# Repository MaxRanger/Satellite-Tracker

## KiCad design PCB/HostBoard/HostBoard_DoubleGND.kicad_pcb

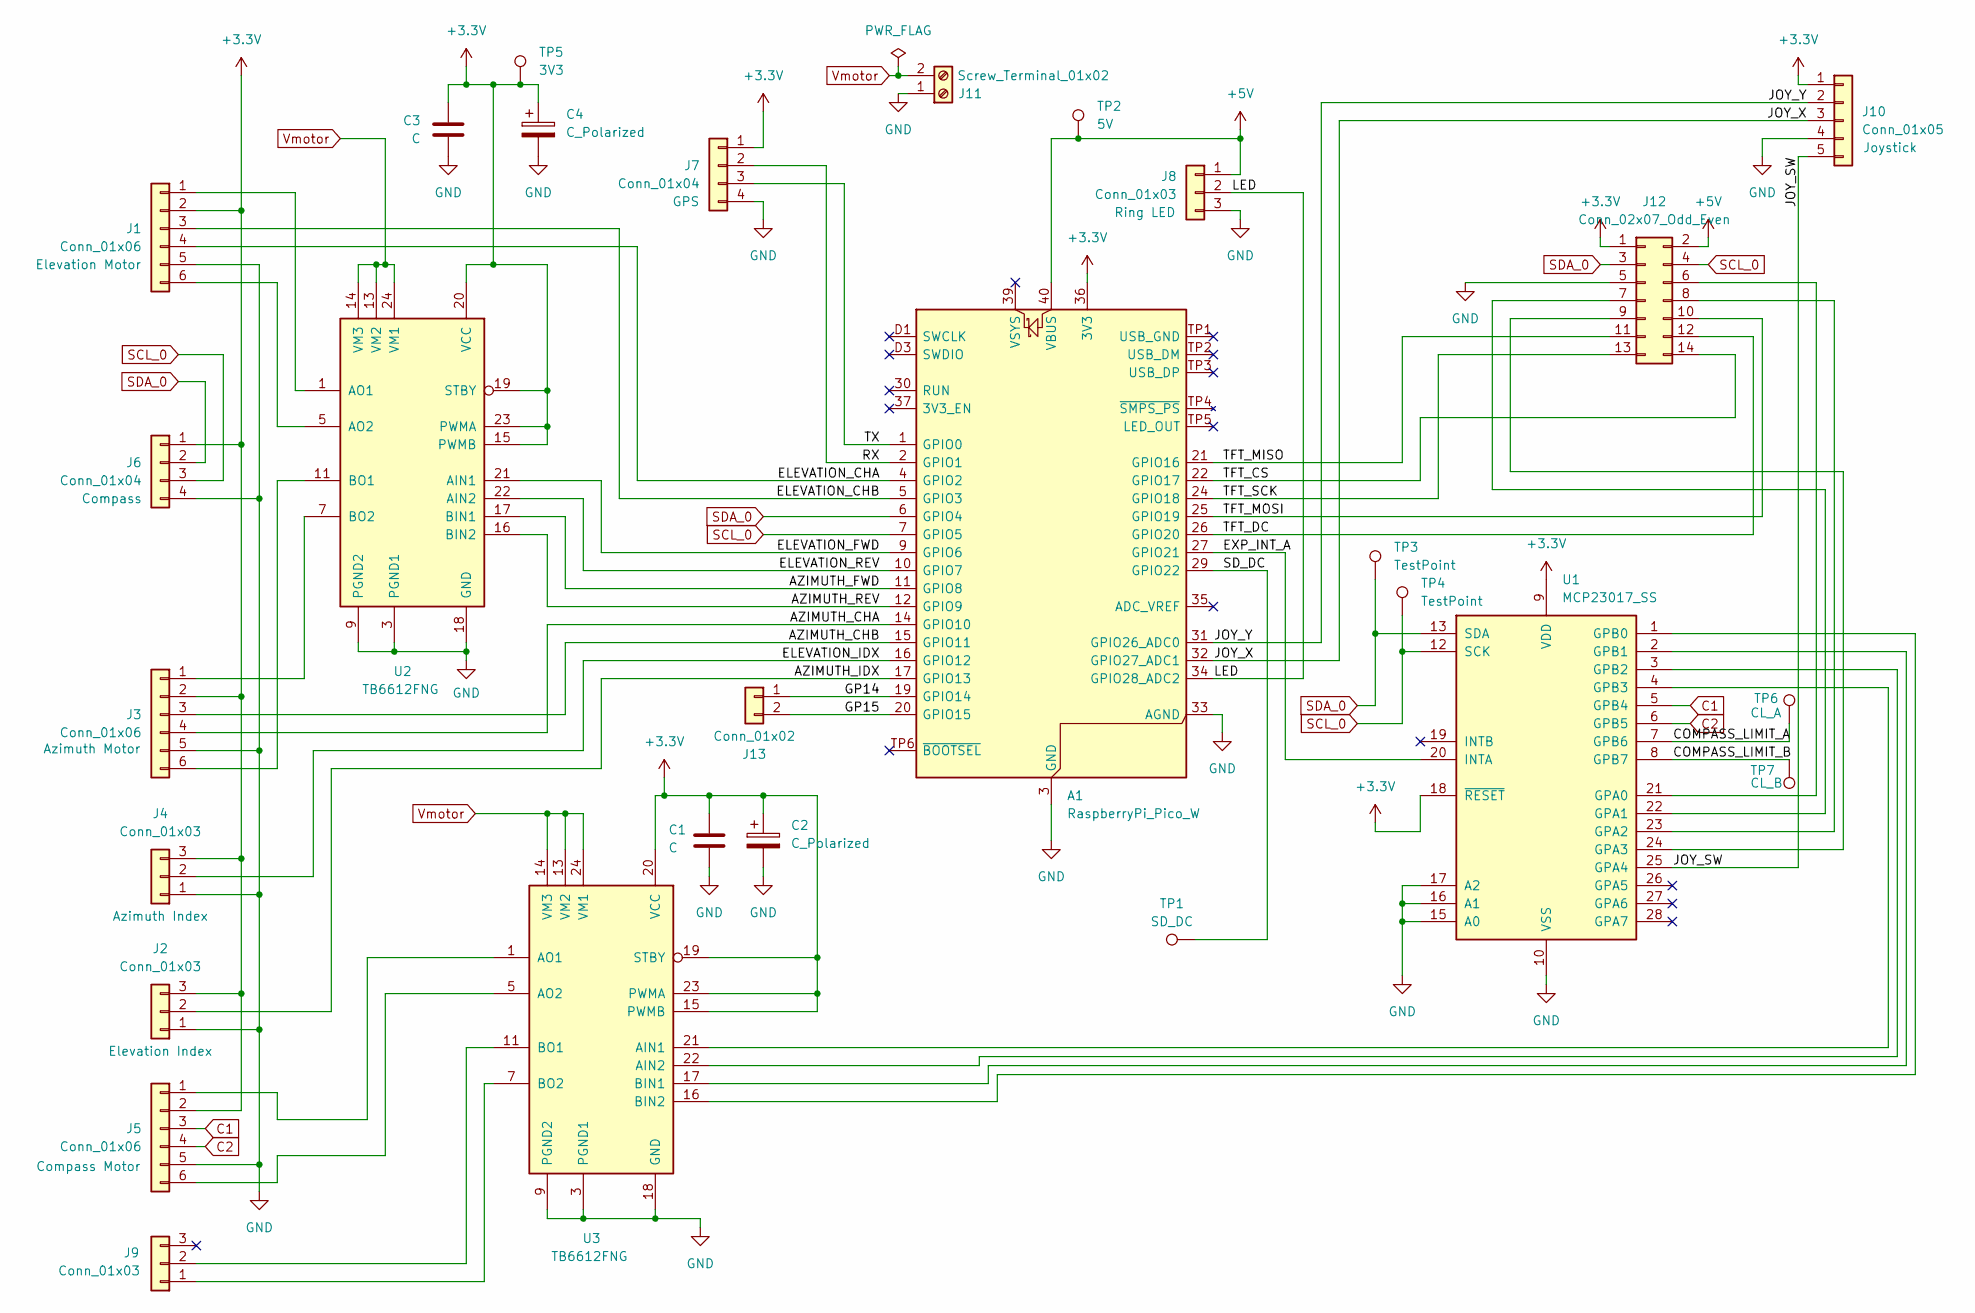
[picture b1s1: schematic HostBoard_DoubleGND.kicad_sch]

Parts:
A1: RaspberryPi_Pico_W; RaspberryPi_Pico_Common_THT
C1, C3: C; C_0805_2012Metric_Pad1.18x1.45mm_HandSolder
C2, C4: C_Polarized; C_0805_2012Metric_Pad1.18x1.45mm_HandSolder
J1, J3, J5: Conn_01x06; JST_EH_S6B-EH_1x06_P2.50mm_Horizontal
J2, J4, J8: Conn_01x03; JST_EH_S3B-EH_1x03_P2.50mm_Horizontal
J6, J7: Conn_01x04; JST_EH_S4B-EH_1x04_P2.50mm_Horizontal
J9: Conn_01x03; PinHeader_1x03_P2.54mm_Vertical
J10: Conn_01x05; JST_EH_S5B-EH_1x05_P2.50mm_Horizontal
J11: Screw_Terminal_01x02; TerminalBlock_Xinya_XY308-2.54-2P_1x02_P2.54mm_Horizontal
J12: Conn_02x07_Odd_Even; PinHeader_2x07_P2.54mm_Vertical
J13: Conn_01x02; PinHeader_1x02_P2.54mm_Vertical
TP1: SD_DC; PinHeader_1x01_P2.54mm_Vertical
TP2: 5V; PinHeader_1x01_P2.54mm_Vertical
TP3, TP4: TestPoint; TestPoint_Pad_1.0x1.0mm
TP5: 3V3; PinHeader_1x01_P2.54mm_Vertical
TP6: CL_A; TestPoint_Pad_1.0x1.0mm
TP7: CL_B; TestPoint_Pad_1.0x1.0mm
U1: MCP23017_SS; SSOP-28_5.3x10.2mm_P0.65mm
U2, U3: TB6612FNG; SSOP-24_5.3x8.2mm_P0.65mm

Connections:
+3.3V: A1.36 (3V3), C1.1, C2.1, C3.1, C4.1, J1.2, J2.3, J3.2, J4.3, J5.2, J6.1, J7.1, J10.1, J12.1, TP5.1, U1.9 (VDD), U1.18 (~RESET), U2.15 (PWMB), U2.19 (STBY), U2.20 (VCC), U2.23 (PWMA), U3.15 (PWMB), U3.19 (STBY), U3.20 (VCC), U3.23 (PWMA)
+5V: A1.40 (VBUS), J8.1, J12.2, TP2.1
/AZIMUTH_CHA: A1.14 (GPIO10), J3.4
/AZIMUTH_CHB: A1.15 (GPIO11), J3.3
/AZIMUTH_FWD: A1.11 (GPIO8), U2.17 (BIN1)
/AZIMUTH_IDX: A1.17 (GPIO13), J2.2
/AZIMUTH_REV: A1.12 (GPIO9), U2.16 (BIN2)
/COMPASS_LIMIT_A: TP6.1, U1.7 (GPB6)
/COMPASS_LIMIT_B: TP7.1, U1.8 (GPB7)
/ELEVATION_CHA: A1.4 (GPIO2), J1.4
/ELEVATION_CHB: A1.5 (GPIO3), J1.3
/ELEVATION_FWD: A1.9 (GPIO6), U2.21 (AIN1)
/ELEVATION_IDX: A1.16 (GPIO12), J4.2
/ELEVATION_REV: A1.10 (GPIO7), U2.22 (AIN2)
/EXP_INT_A: A1.27 (GPIO21), U1.20 (INTA)
/GP14: A1.19 (GPIO14), J13.1
/GP15: A1.20 (GPIO15), J13.2
/JOY_SW: J10.5, U1.25 (GPA4)
/JOY_X: A1.32 (GPIO27_ADC1), J10.3
/JOY_Y: A1.31 (GPIO26_ADC0), J10.2
/LED: A1.34 (GPIO28_ADC2), J8.2
/RX: A1.2 (GPIO1), J7.2
/SD_DC: A1.29 (GPIO22), TP1.1
/TFT_CS: A1.22 (GPIO17), J12.14
/TFT_DC: A1.26 (GPIO20), J12.12
/TFT_MISO: A1.21 (GPIO16), J12.11
/TFT_MOSI: A1.25 (GPIO19), J12.10
/TFT_SCK: A1.24 (GPIO18), J12.13
/TX: A1.1 (GPIO0), J7.3
C1: J5.3, U1.5 (GPB4)
C2: J5.4, U1.6 (GPB5)
GND: A1.3 (GND), A1.8 (GND), A1.13 (GND), A1.18 (GND), A1.23 (GND), A1.28 (GND), A1.33 (AGND), A1.38 (GND), A1.D2 (GND), C1.2, C2.2, C3.2, C4.2, J1.5, J2.1, J3.5, J4.1, J5.5, J6.4, J7.4, J8.3, J10.4, J11.1, J12.5, U1.10 (VSS), U1.15 (A0), U1.16 (A1), U1.17 (A2), U2.3 (PGND1), U2.4 (PGND1), U2.9 (PGND2), U2.10 (PGND2), U2.18 (GND), U3.3 (PGND1), U3.4 (PGND1), U3.9 (PGND2), U3.10 (PGND2), U3.18 (GND)
unnamed: J1.1, U2.1 (AO1), U2.2 (AO1)
unnamed: J1.6, U2.5 (AO2), U2.6 (AO2)
unnamed: J3.1, U2.7 (BO2), U2.8 (BO2)
unnamed: J3.6, U2.11 (BO1), U2.12 (BO1)
unnamed: J5.1, U3.1 (AO1), U3.2 (AO1)
unnamed: J5.6, U3.5 (AO2), U3.6 (AO2)
unnamed: J9.1, U3.7 (BO2), U3.8 (BO2)
unnamed: J9.2, U3.11 (BO1), U3.12 (BO1)
unnamed: J12.6, U1.21 (GPA0)
unnamed: J12.7, U1.22 (GPA1)
unnamed: J12.8, U1.23 (GPA2)
unnamed: J12.9, U1.24 (GPA3)
unnamed: U1.1 (GPB0), U3.16 (BIN2)
unnamed: U1.2 (GPB1), U3.17 (BIN1)
unnamed: U1.3 (GPB2), U3.22 (AIN2)
unnamed: U1.4 (GPB3), U3.21 (AIN1)
SCL_0: A1.7 (GPIO5), J6.3, J12.4, TP4.1, U1.12 (SCK)
SDA_0: A1.6 (GPIO4), J6.2, J12.3, TP3.1, U1.13 (SDA)
Vmotor: J11.2, U2.13 (VM2), U2.14 (VM3), U2.24 (VM1), U3.13 (VM2), U3.14 (VM3), U3.24 (VM1)

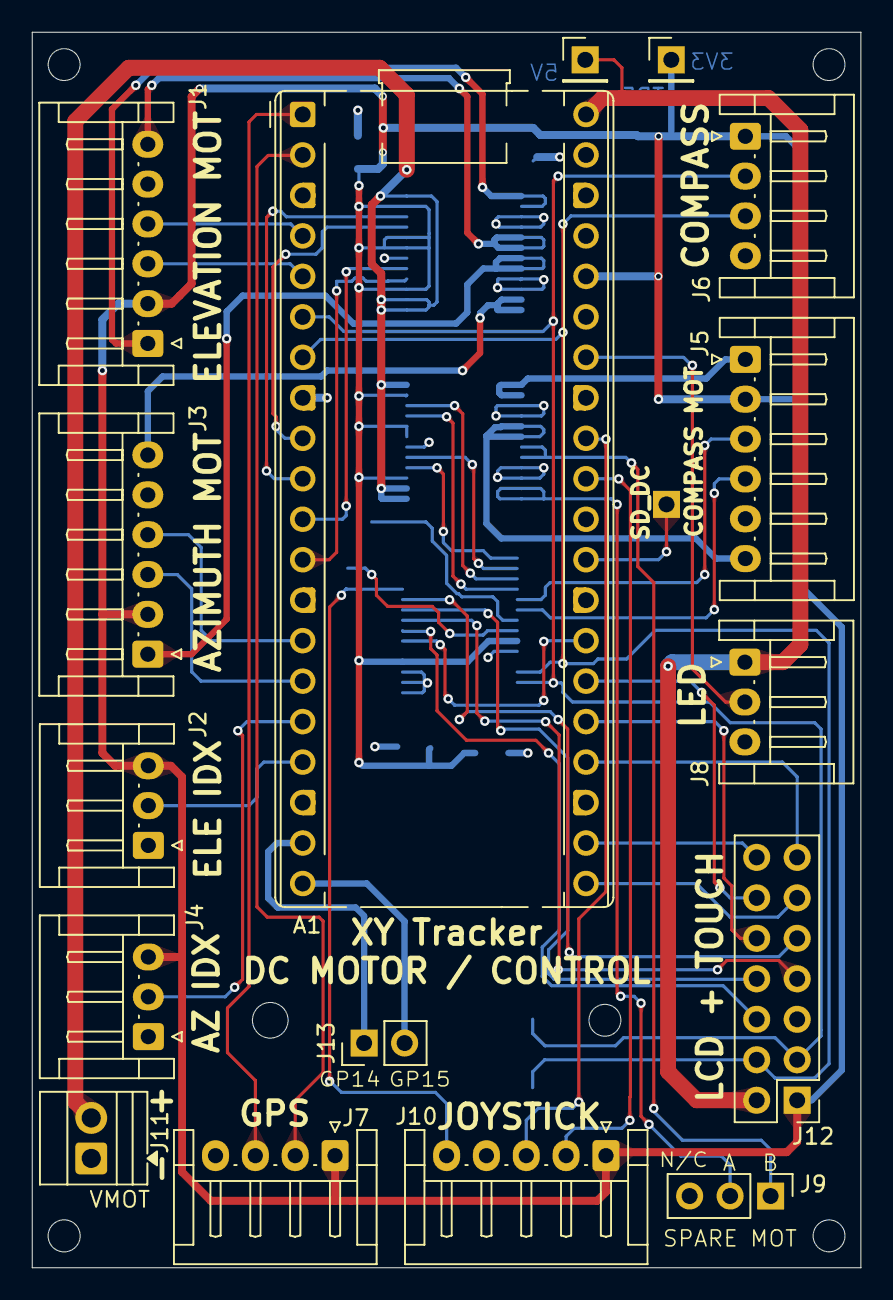
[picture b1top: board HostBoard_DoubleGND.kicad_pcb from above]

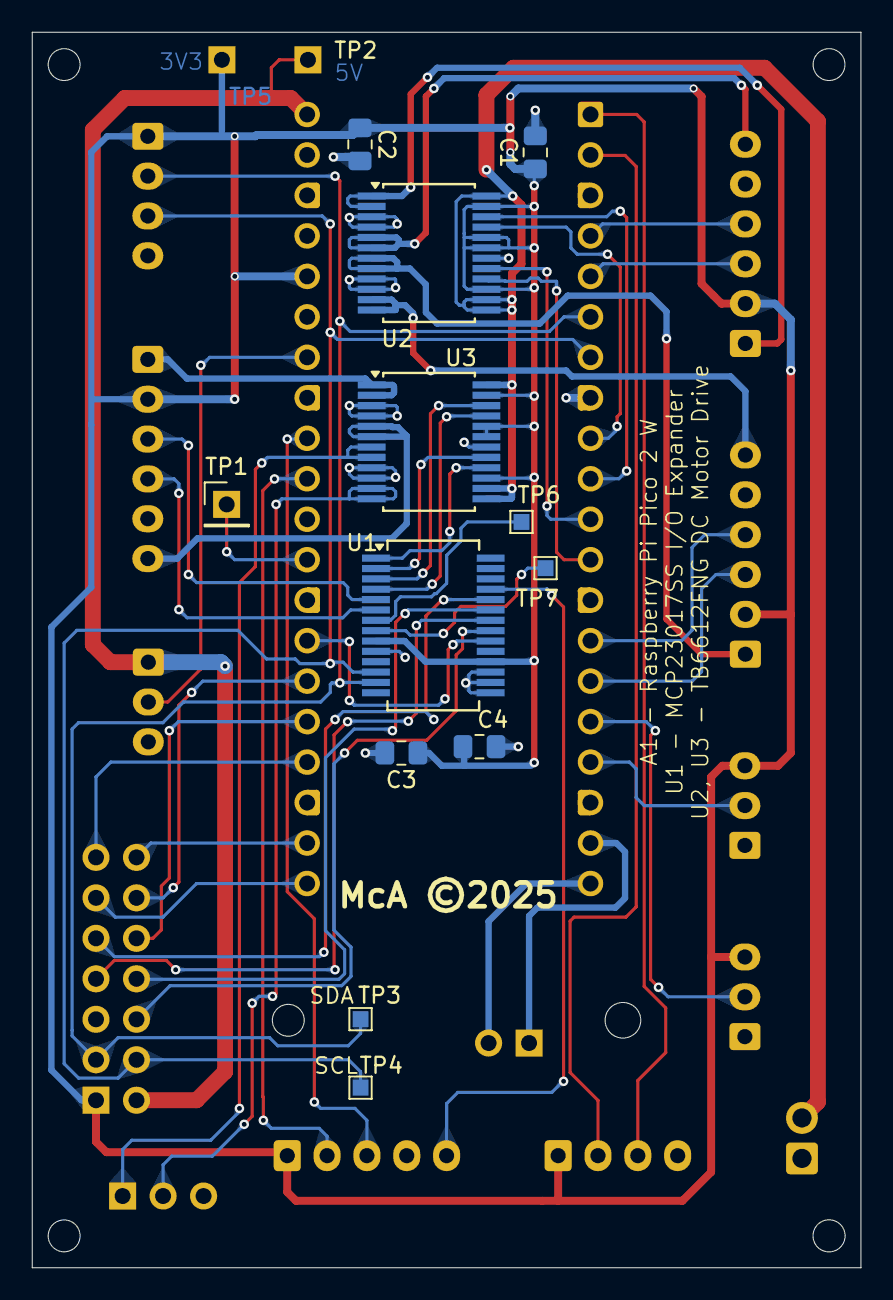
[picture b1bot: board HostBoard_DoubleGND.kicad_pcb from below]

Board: 4 copper layers, 52.0 x 77.5 mm, 28 parts (12 on the bottom side), 51 nets.

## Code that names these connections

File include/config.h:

/*
 * config.h - Configuration and Pin Definitions
 */

#ifndef CONFIG_H
#define CONFIG_H


// ============================================================================
// Cables and Connectors for prototype model 1
// ============================================================================
// Joystick - 5 pin. BLACK=GND, WHITE=VCC, GREY=X[GP26 (ADC0) Pin 32], PURPLE=Y[GP27 (ADC1) Pin 31], BLUE=Button
// GPS: 5 pin. GREEN=VCC, YELLOW=GND, ORANGE=TX (GP1/Pin2), RED=RX (GP0/Pin1), BROWN=PPS
// LED: 3 pin. WHITE=GND, WHITE/LONG RED STRIPES=+5v, WHITE/SHORT RED STRIPES=DATA IN (DI) (DO = N/C)
// Index: 2x 3-pin. Elevation-Red=VCC / Orange=GND, Pink/White=Signal  Azimuth-Red=VCC / Blue=GND, Yellow=Signal
// Motor RED=M2, BLACK=GND, YELLOW=C2, GREEN=C1, BLUE=GND, WHITE=M1  1:298 elevation, 1:xx + 1:3 azimuth
// Compass:
// ===========================================================================


// ============================================================================
// PIN DEFINITIONS
// ============================================================================

// Motor Control Pins
#define MOTOR_E_PWM_FWD    6
#define MOTOR_E_PWM_REV    7
#define MOTOR_A_PWM_FWD    8
#define MOTOR_A_PWM_REV    9

// Motor Driver Enable Pins (optional, depends on driver type)
#define MOTOR_E_ENABLE     12
#define MOTOR_A_ENABLE     13

// Encoder Pins (must be consecutive for PIO)
#define ENCODER_E_BASE     2   // E_A=2, E_B=3
#define ENCODER_A_BASE     10  // A_A=10, A_B=11

// Index Sensor Pins
#define INDEX_E            24
#define INDEX_A            25 

// Emergency Stop Pin (active low with internal pullup)
#define EMERGENCY_STOP_PIN 23  // GP23 (joystick button)

// GPS Serial (UART0)
#define GPS_RX             1   // GP1 Pin 2 (UART0 RX)
#define GPS_TX             0   // GP0 Pin 1 (UART0 TX)

// Adafruit 2.8" TFT Display (PID 2423) - ILI9341 with FT6206 Touch
#define TFT_MOSI           19  // GP19 Pin 25 (SPI TX)
#define TFT_MISO           16  // GP16 Pin 21 (SPI RX)
#define TFT_SCK            18  // GP18 Pin 24 (SPI SCK)
#define TFT_CS             17  // GP17 Pin 22 (Chip Select)
#define TFT_DC             14  // GP14 (Data/Command)

// FT6206 Capacitive Touch (I2C)
#define TOUCH_SDA          4   // GP4 Pin 6 (I2C SDA)
#define TOUCH_SCL          5   // GP5 Pin 7 (I2C SCL)

// I2C for QMC5883L Magnetometer (shares bus with touch - different I2C addresses)
#define I2C_SDA            4   // GP4 Pin 6 (Shared with TOUCH_SDA)
#define I2C_SCL            5   // GP5 Pin 7 (Shared with TOUCH_SCL)

// Hardware Buttons (4 momentary switches on LCD module)
#define BUTTON_1_PIN       20  // GP20 Pin 26
#define BUTTON_2_PIN       21  // GP21 Pin 27
#define BUTTON_3_PIN       15  // GP15 Pin 20
#define BUTTON_4_PIN       29  // GP29 Pin 35

// WS2812 LED Ring (50 LEDs)
#define LED_DATA_PIN       28  // GP28 Pin 34

// Analog Joystick (X/Y only, button used for E-Stop)
#define JOYSTICK_Y_PIN     26  // GP26 (ADC0) Pin 31
#define JOYSTICK_X_PIN     27  // GP27 (ADC1) Pin 32
#define JOYSTICK_BTN_PIN   99  // unused (E-Stop uses EMERGENCY_STOP_PIN)

// SD Card (SPI, shares bus with display)
#define SD_CS_PIN          22  // GP22 Pin 29

// PI 31 -> LCD 9 

// NOTE: Magnetometer and touch screen share I2C bus
// This is OK because they have different I2C addresses:
// - FT6206 touch: 0x38
// - QMC5883L magnetometer: 0x0D
// Both can coexist on the same I2C bus

// ============================================================================
// MOTOR DRIVER CONFIGURATION
// ============================================================================

// Select your motor driver type (uncomment ONE)
#define MOTOR_DRIVER_TB6612FNG

#ifdef MOTOR_DRIVER_L298N
  #define MOTOR_USE_ENABLE_PINS true
  #define MOTOR_ENABLE_ACTIVE_HIGH true
  #define MOTOR_MIN_PWM 50
  #define MOTOR_BRAKE_MODE false
#endif

#ifdef MOTOR_DRIVER_TB6612FNG
  #define MOTOR_USE_ENABLE_PINS false
  #define MOTOR_ENABLE_ACTIVE_HIGH true
  #define MOTOR_MIN_PWM 0
  #define MOTOR_BRAKE_MODE true
#endif

#ifdef MOTOR_DRIVER_DRV8833
  #define MOTOR_USE_ENABLE_PINS false
  #define MOTOR_MIN_PWM 0
  #define MOTOR_BRAKE_MODE true
#endif

#ifdef MOTOR_DRIVER_GENERIC
  #define MOTOR_USE_ENABLE_PINS false
  #define MOTOR_MIN_PWM 0
  #define MOTOR_BRAKE_MODE false
#endif

// ============================================================================
// SYSTEM CONFIGURATION
// ============================================================================

// WiFi credentials are now configured via display setup screen
// No hardcoded credentials needed!

// Mechanical Configuration
#define GEAR_RATIO 75.0
#define ENCODER_PPR 1
#define DEGREES_PER_PULSE (360.0 / (GEAR_RATIO * ENCODER_PPR * 4))

// PID Parameters
#define KP 3.0
#define KI 0.15
#define KD 0.8
#define MAX_ERROR_INTEGRAL 50.0
#define POSITION_TOLERANCE 0.3

// Timing
#define CONTROL_LOOP_HZ 100.0
#define CONTROL_LOOP_DT (1.0 / CONTROL_LOOP_HZ)
#define TRACKING_UPDATE_MS ((unsigned long)(CONTROL_LOOP_DT * 1000))
#define DISPLAY_UPDATE_MS 500

// Safety Limits (with 5 degree margin for detection)
#define MAX_ELEVATION 90.0
#define MIN_ELEVATION 0.0

// Display Settings
#define SCREEN_WIDTH  320
#define SCREEN_HEIGHT 240
#define STATUS_BAR_HEIGHT 30
#define BUTTON_HEIGHT 50
#define BUTTON_MARGIN 10

// PWM Configuration
#define PWM_FREQUENCY 20000
#define PWM_RESOLUTION 8

// GPS Configuration
#define GPS_TIMEOUT_MS 10000  // 10 seconds without valid fix

#endif // CONFIG_H

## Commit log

2025-10-14 Refactor and enhance various modules: improved PIO encoder handling, added emergency stop functionality, refined GPS and tracking logic, and implemented a settings screen in the display module.
2025-10-15 Add stubs for the 4 momentary-contact switches on the LCD display module Move compass-related code to the compass module Add 2812 LED driver from PIO to give user state information
2025-10-15 Add Joystick for manual control
2025-10-15 Move pin assignments to avoid conflicts
2025-10-16 Add initial attempt at mDNS. Not working on Pixel 9 Android cell phone
    Fix problem - web server not started when WiFi is up
2025-10-17 Begin adding flash storage capability Add predictive tracking_logic Fix GPS communication to Serial 1
2025-10-17 Add chron0
2025-10-21 Move all serial interface code to module Add better serial monitor Deconflict GPIO pins
2025-10-21 Add touchscreen WiFi setup, on-screen keyboard Update serial banner with build timestamp
2025-10-21 Improve buffer overflow protection
2025-10-22 Add LED commands to the interactive serial console
2025-10-22 Debug 2812 LED ring
2025-10-22 Add better password security for webserver
2025-10-22 Add more 2812 Ring LED debug info
2025-10-23 Fix LEDs. Still need to understand PIO shift out register, RGB vs BRG vs GRB bit ordering
2025-10-30 Move status output from serial to corresponding modules.
2025-10-30 Trying to get reprogram with having to press BOOT button. No luck.
2025-11-04 Add Host PCB. Will include Raspberry Pi Pico 2 W, motor controller, connectors for motors / axis index / joystick / GPS / compass / LCD / USB-C
2025-11-07 Minor notes and debugging changes
2025-11-07 Add routing and second motor controller for automatic compass calibration. Without ability to multistep, not adding connectors for dual-use stepper motor / DC motor option.
2025-11-11 Continuing schematic entry
2025-11-11 Add interactive motor debug for tuning PID
2025-11-11 Cleanup and reorganization
2025-11-12 Footprints assigned. Start PCB layout. Need to finish tentative schematics pin assignments
2025-11-13 PCB Routing. Signals done except VMot and TPx. Need power planes, silk and outline
2025-11-14 Completed PCB for existing schematic, need to re-assign LCD and check schematic
2025-11-15 Moved TFT_DC and Expander INTA pins to match code
2025-11-18 Add new PCB layout with two ground planes, no power planes, routing in N-S and E-W on top and bottom
2025-11-19 As sent to JLBPCB. $66.
2025-11-19 Renamed PCB with power plane. Note that this version is behind the double-ground version and is not intended to be updated. Double-ground was sent for manufacturing on 2025-Nov-18

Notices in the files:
PCB/HostBoard/HostBoard_DoubleGND.kicad_pcb:
McA ©2025
